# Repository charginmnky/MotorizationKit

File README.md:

# MotorizationKit
custom PCB with connectors that make wiring on my motorized iron man helmet simpler and easier, also allowing for easier flexibility

I made the schematic for the PCB. I used KiCad, and I am going to be using an Arduino Nano. Whilst wiring, I had to do extensive research on what parts I am using and which pins connect to what.

I then assigned footprints. I will be using 2_pin JST micro ports and then 2 3-pin jumper pins.

This all took me 1hr and 42 minutes.

I created/designed my PCB and routed it. I used both the back and front of the PCB to keep wiring as clean as possible, and I rounded the corners of the PCB using Edge Cuts so that corners of the PCB were not sharp.

I then added 3D models to my board in KiCad's 3D viewer to visualize the PCB and see what it looks like.

Using the 3D models helped me identify what exact parts that I need to use, which will be my next step. 

Altogether, all of this took 2hrs AND 36 minutes.

I researched the products that I am going to use on the PCB.

For the Arduino Uno, I found a cheap USB-C one from Ali Express with free shipping, which is the one I have chosen:

I then researched the 2-pin JST micro connectors for the PCB. For these, I specifically looked out for right angle connectors so that when on the PCB and wires are plugged in, they stay compact and come out the side of the PC, allowing the PCB to fit comfortably in the helmet.

For the wires that would plug into the micro connectors, I found some on Ali Express that would be suitable and would fit.

Finally, for the 3-pin connectors for the servo motors, I have chosen simple break-off jumper pins, that will connect to the stock connectors on the servos, which I will not be buying as I already have them.

This all took me 1 hour and 40 minutes.

I redesigned my circuit in Tinkercad to make it easier for me to understand the circuit.

I had to use an Arduino micro in the diagram because I could not find the Arduino Nano in the application. 

This took me an hour and 47 minutes.

I added all the parts I need to my cart to add up the total price.

I now know my budget for my project, and it will be Tier 5, at about 20 pounds.

I also uploaded my prod.zip folder to JLCPCB to get a quote for the PCB.

Here are all the links to the individual parts:

Arduino Nano ---- https://shorturl.at/JPrPM

2-pin JST connectors ---- https://shorturl.at/tX3ts

2-pin JST male connectors ---- https://shorturl.at/IjD5K

Break-off pins ---- https://shorturl.at/FqSn6

Housing foam ---- https://shorturl.at/O2BPj

Adding the prices together only took me around 10 minutes.

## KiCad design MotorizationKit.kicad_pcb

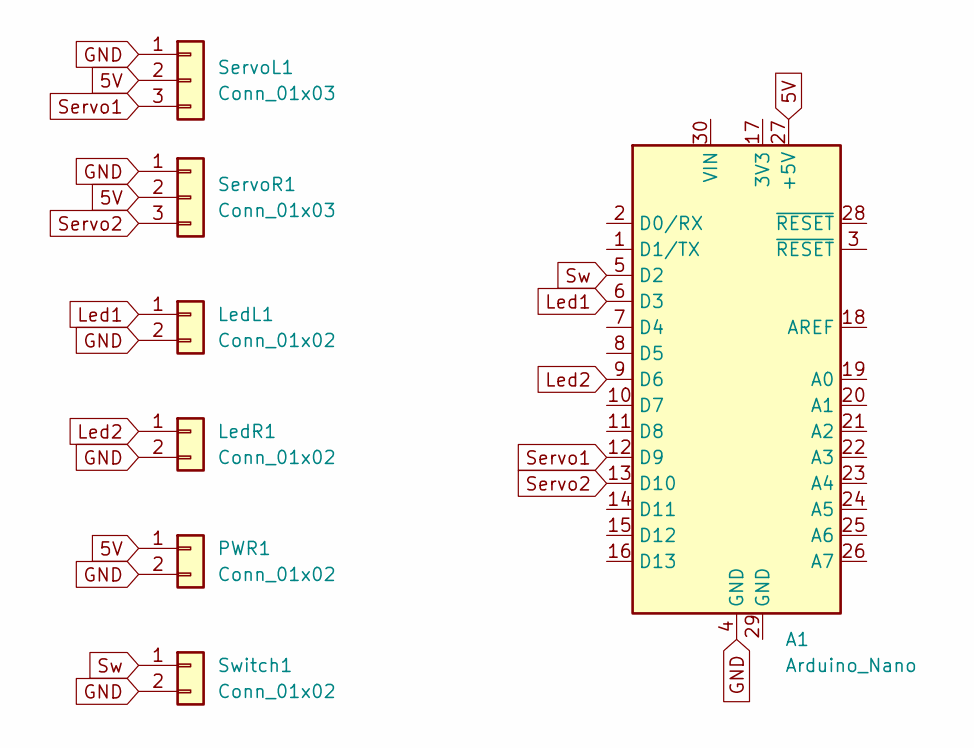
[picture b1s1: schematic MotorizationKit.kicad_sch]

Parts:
A1: Arduino_Nano
LedL1: Conn_01x02; JST_PH_S2B-PH-K_1x02_P2.00mm_Horizontal
LedR1: Conn_01x02; JST_PH_S2B-PH-K_1x02_P2.00mm_Horizontal
PWR1: Conn_01x02; JST_PH_S2B-PH-K_1x02_P2.00mm_Horizontal
ServoL1: Conn_01x03; PinHeader_1x03_P2.54mm_Vertical
ServoR1: Conn_01x03; PinHeader_1x03_P2.54mm_Vertical
Switch1: Conn_01x02; JST_PH_S2B-PH-K_1x02_P2.00mm_Horizontal

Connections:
5V: A1.27 (+5V), PWR1.1, ServoL1.2, ServoR1.2
GND: A1.4 (GND), LedL1.2, LedR1.2, PWR1.2, ServoL1.1, ServoR1.1, Switch1.2
Led1: A1.6 (D3), LedL1.1
Led2: A1.9 (D6), LedR1.1
Servo1: A1.12 (D9), ServoL1.3
Servo2: A1.13 (D10), ServoR1.3
Sw: A1.5 (D2), Switch1.1

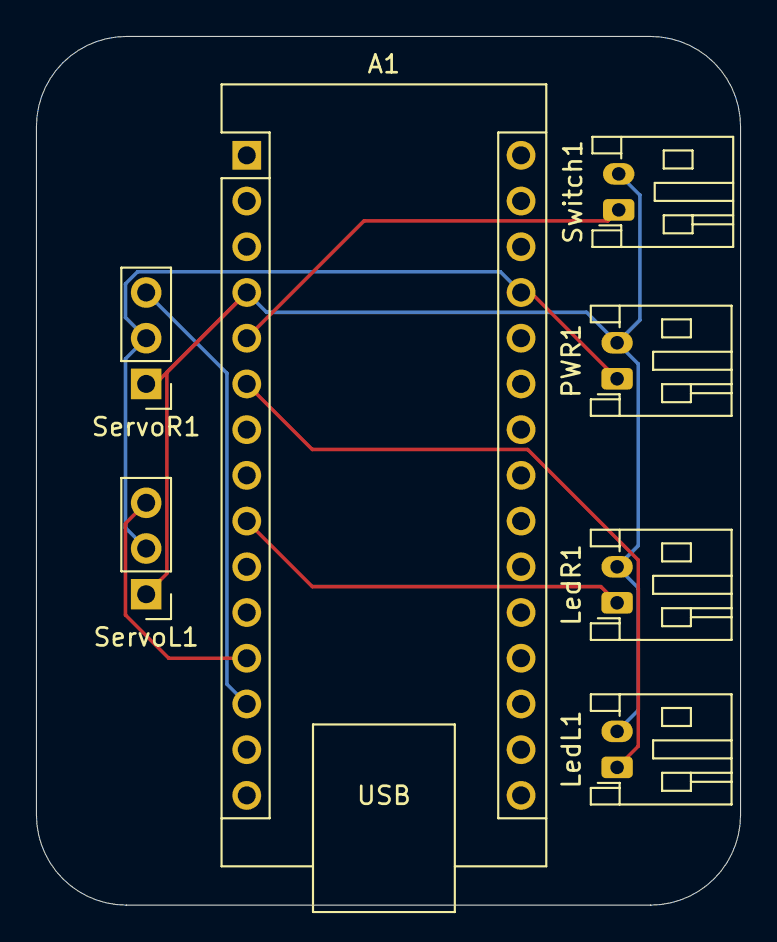
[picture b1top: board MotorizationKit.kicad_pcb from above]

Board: 2 copper layers, 39.1 x 48.3 mm, 7 parts (0 on the bottom side), 7 nets.
